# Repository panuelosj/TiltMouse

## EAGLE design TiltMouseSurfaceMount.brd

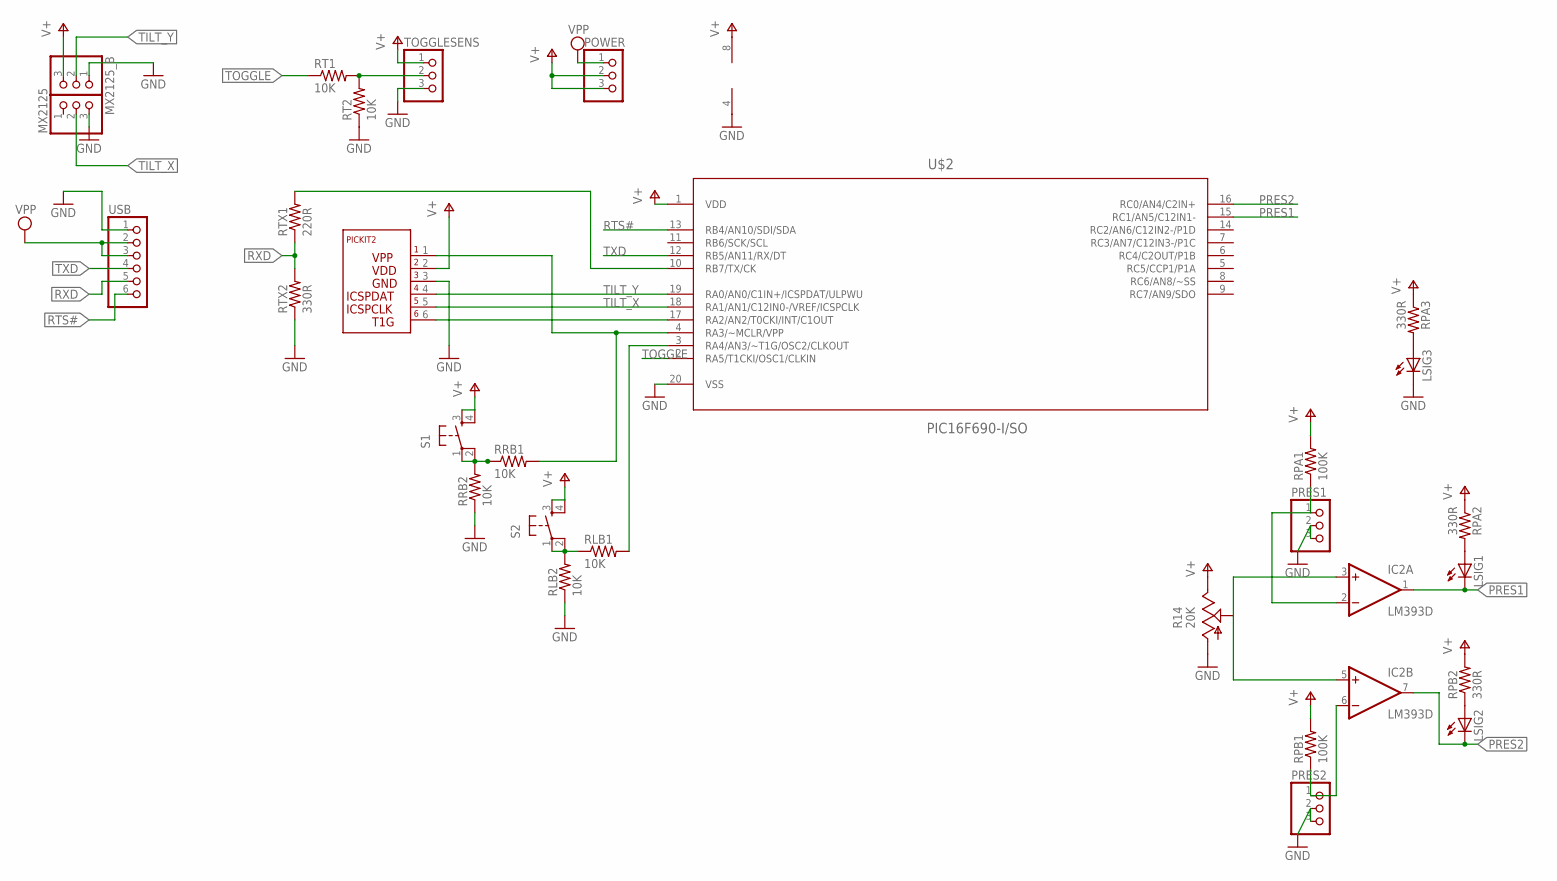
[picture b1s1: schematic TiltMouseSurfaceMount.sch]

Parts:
IC2: LM393D; SO08
LSIG1, LSIG2, LSIG3: LEDSMT1206; 1206
MX2125, MX2125_B: PINHD-1X3; 1X03
POWER: PINHD-1X3; 1X03
PRES1, PRES2: PINHD-1X3/90; 1X03/90
R14: 20K; SM-42/43A
RLB1, RLB2: 10K; R0805
RPA1: 100K; R0805
RPA2, RPA3: 330R; R0805
RPB1: 100K; R0805
RPB2: 330R; R0805
RRB1, RRB2: 10K; R0805
RT1, RT2: 10K; R0805
RTX1: 220R; R0805
RTX2: 330R; R0805
S1, S2: TAC_SWITCHSMD; TACTILE_SWITCH_SMD
TOGGLESENS: PINHD-1X3; 1X03
U$2: PIC16F690-I/SO; SOIC127P1030X265-20N
U$3: PICKIT-ICSP; PICKITJUMPER
USB: PINHD-1X6/90; 1X06/90

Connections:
GND: IC2.4 (V-), LSIG3.C, MX2125.3, MX2125_B.1, PRES1.2, PRES1.3, PRES2.2, PRES2.3, R14.1 (A), RLB2.1, RRB2.1, RT2.1, RTX2.1, TOGGLESENS.3, U$2.20 (VSS), U$3.3, USB.1
unnamed: RT1.2, RT2.2, TOGGLESENS.2
unnamed: IC2.2 (-IN), PRES1.1, RPA1.1
unnamed: RTX1.2, U$2.10 (RB7/TX/CK)
unnamed: RRB1.1, RRB2.2, S1.1, S1.2
unnamed: RLB1.1, RLB2.2, S2.1, S2.2
unnamed: RLB1.2, U$2.3 (RA4/AN3/~T1G/OSC2/CLKOUT)
unnamed: IC2.6 (-IN), PRES2.1, RPB1.1
unnamed: IC2.3 (+IN), IC2.5 (+IN), R14.2 (S)
unnamed: LSIG2.A, RPB2.1
unnamed: LSIG1.A, RPA2.2
unnamed: LSIG3.A, RPA3.2
unnamed: RRB1.2, U$2.4 (RA3/~MCLR/VPP), U$3.1
unnamed: U$2.17 (RA2/AN2/T0CKI/INT/C1OUT), U$3.6
PRES1: IC2.1 (OUT), LSIG1.C, U$2.15 (RC1/AN5/C12IN1-)
PRES2: IC2.7 (OUT), LSIG2.C, U$2.16 (RC0/AN4/C2IN+)
RTS#: U$2.13 (RB4/AN10/SDI/SDA), USB.6
RXD: RTX1.1, RTX2.2, USB.5
TILT_X: MX2125.2, U$2.18 (RA1/AN1/C12IN0-/VREF/ICSPCLK), U$3.5
TILT_Y: MX2125_B.2, U$2.19 (RA0/AN0/C1IN+/ICSPDAT/ULPWU), U$3.4
TOGGLE: RT1.1, U$2.2 (RA5/T1CKI/OSC1/CLKIN)
TXD: U$2.12 (RB5/AN11/RX/DT), USB.4
V+: IC2.8 (V+), MX2125_B.3, POWER.2, POWER.3, R14.3 (E), RPA1.2, RPA2.1, RPA3.1, RPB1.2, RPB2.2, S1.3, S1.4, S2.3, S2.4, TOGGLESENS.1, U$2.1 (VDD), U$3.2
VPP: POWER.1, USB.2, USB.3

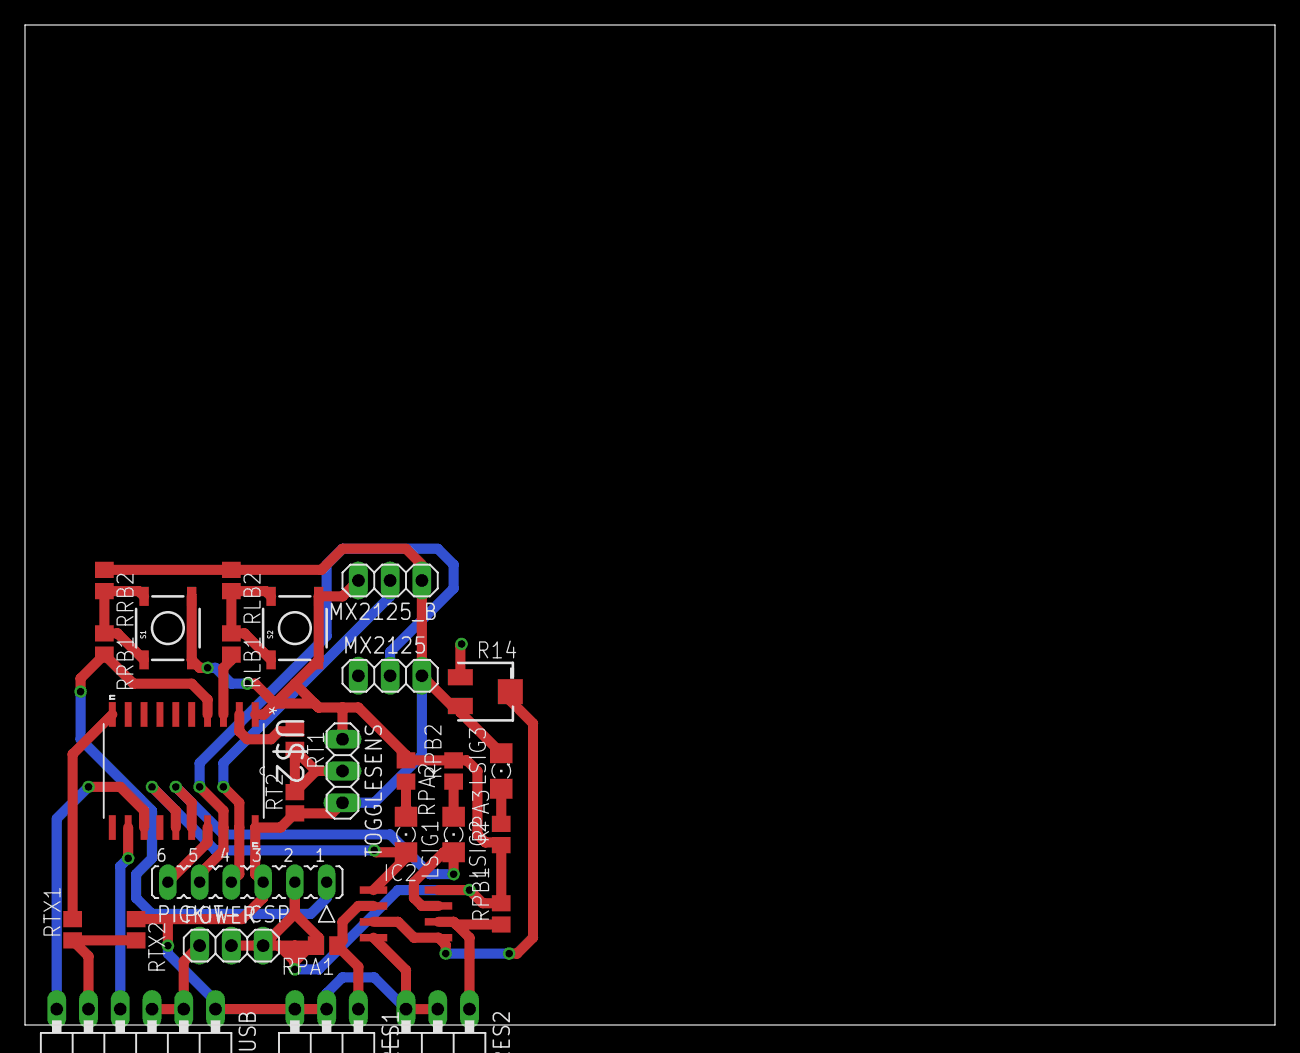
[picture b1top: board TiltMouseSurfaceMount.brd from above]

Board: 2 copper layers, 100.0 x 80.0 mm, 29 parts (0 on the bottom side), 24 nets.

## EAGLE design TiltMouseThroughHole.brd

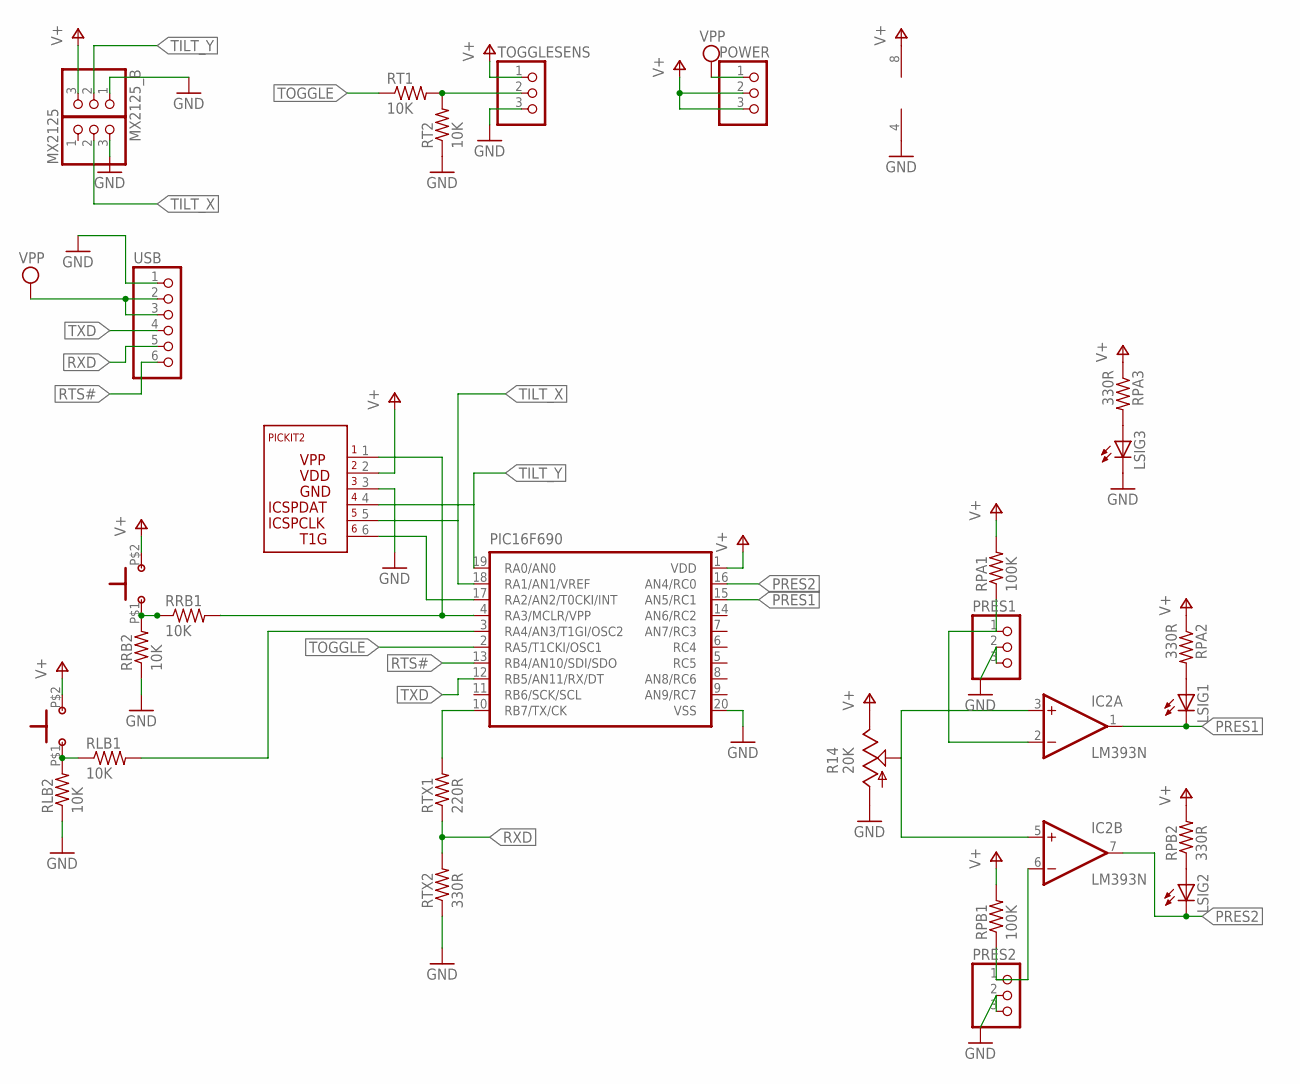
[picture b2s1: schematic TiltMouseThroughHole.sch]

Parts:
IC2: LM393N; DIL08
LB: PUSHBUTTON
LSIG1, LSIG2, LSIG3: LED5MM
MX2125, MX2125_B: PINHD-1X3; 1X03
PIC16F690: PIC16F6XX; DIL20
POWER: PINHD-1X3; 1X03
PRES1, PRES2: PINHD-1X3/90; 1X03/90
R14: 20K; B25P
RB: PUSHBUTTON
RLB1, RLB2: 10K; 0207/12
RPA1: 100K; 0207/10
RPA2: 330R; 0207/15
RPA3: 330R; 0207/10
RPB1: 100K; 0207/10
RPB2: 330R; 0207/15
RRB1, RRB2: 10K; 0207/12
RT1, RT2: 10K; 0207/10
RTX1: 220R; 0207/15
RTX2: 330R; 0207/15
TOGGLESENS: PINHD-1X3; 1X03
U$1: PICKIT-ICSP; PICKITJUMPER
USB: PINHD-1X6/90; 1X06/90

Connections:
GND: IC2.4 (V-), LSIG3.K (C), MX2125.3, MX2125_B.1, PIC16F690.20 (VSS), PRES1.2, PRES1.3, PRES2.2, PRES2.3, R14.A, RLB2.1, RRB2.1, RT2.1, RTX2.1, TOGGLESENS.3, U$1.3, USB.1
unnamed: PIC16F690.4 (RA3/MCLR/VPP), RRB1.2, U$1.1
unnamed: RT1.2, RT2.2, TOGGLESENS.2
unnamed: IC2.2 (-IN), PRES1.1, RPA1.1
unnamed: PIC16F690.17 (RA2/AN2/T0CKI/INT), U$1.6
unnamed: PIC16F690.10 (RB7/TX/CK), RTX1.2
unnamed: RB.P$1 (1), RRB1.1, RRB2.2
unnamed: LB.P$1 (1), RLB1.1, RLB2.2
unnamed: PIC16F690.3 (RA4/AN3/T1GI/OSC2), RLB1.2
unnamed: IC2.6 (-IN), PRES2.1, RPB1.1
unnamed: IC2.3 (+IN), IC2.5 (+IN), R14.S
unnamed: LSIG2.A, RPB2.1
unnamed: LSIG1.A, RPA2.2
unnamed: LSIG3.A, RPA3.2
PRES1: IC2.1 (OUT), LSIG1.K (C), PIC16F690.15 (AN5/RC1)
PRES2: IC2.7 (OUT), LSIG2.K (C), PIC16F690.16 (AN4/RC0)
RTS#: PIC16F690.13 (RB4/AN10/SDI/SDO), USB.6
RXD: RTX1.1, RTX2.2, USB.5
TILT_X: MX2125.2, PIC16F690.18 (RA1/AN1/VREF), U$1.5
TILT_Y: MX2125_B.2, PIC16F690.19 (RA0/AN0), U$1.4
TOGGLE: PIC16F690.2 (RA5/T1CKI/OSC1), RT1.1
TXD: PIC16F690.12 (RB5/AN11/RX/DT), USB.4
V+: IC2.8 (V+), LB.P$2 (2), MX2125_B.3, PIC16F690.1 (VDD), POWER.2, POWER.3, R14.E, RB.P$2 (2), RPA1.2, RPA2.1, RPA3.1, RPB1.2, RPB2.2, TOGGLESENS.1, U$1.2
VPP: POWER.1, USB.2, USB.3

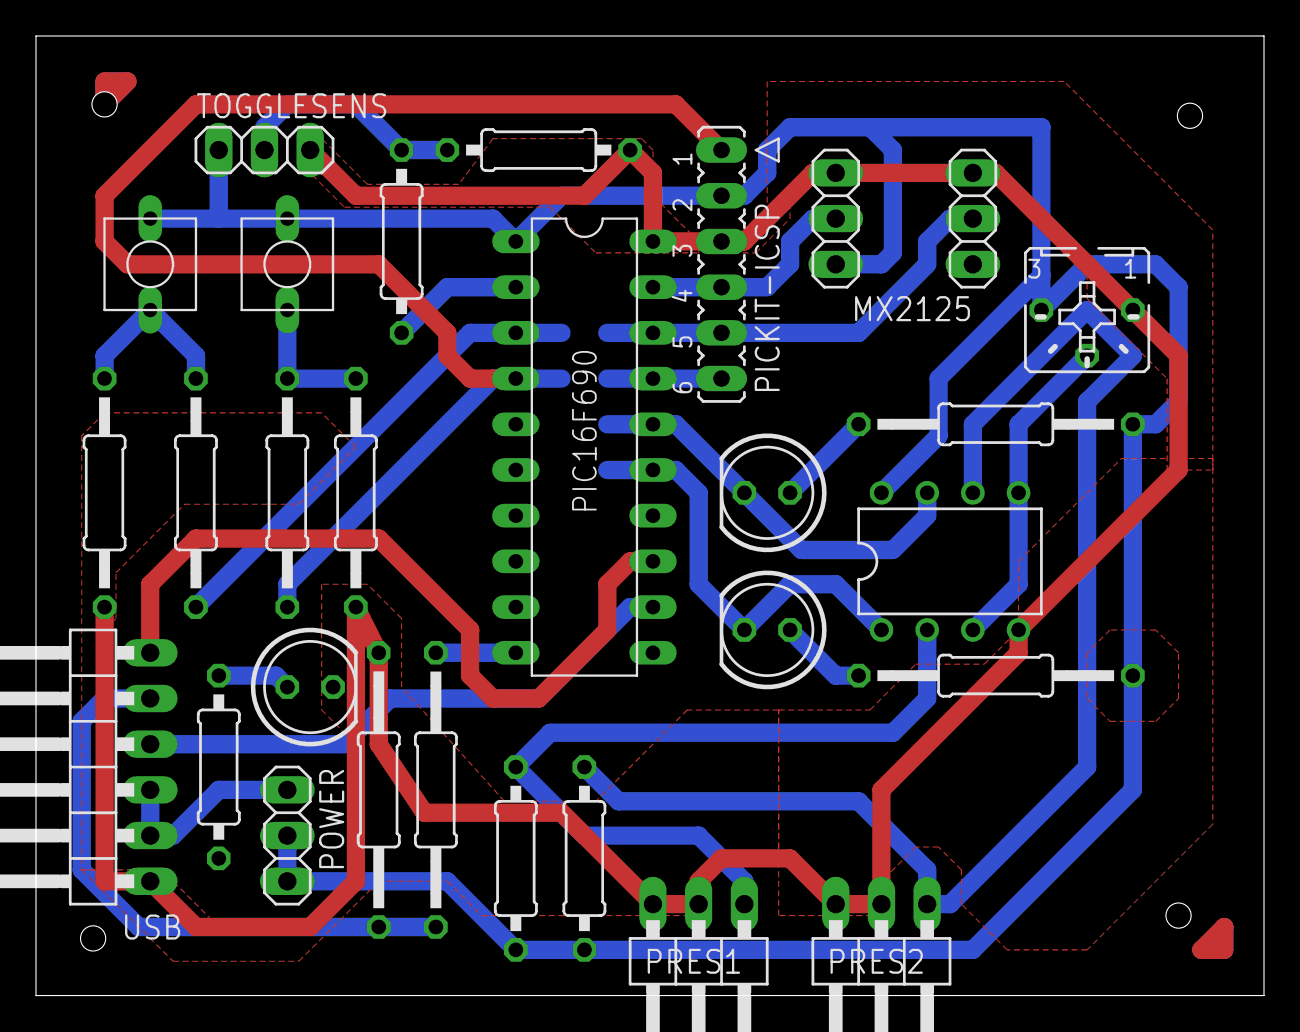
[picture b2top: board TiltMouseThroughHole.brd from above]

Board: 2 copper layers, 68.2 x 53.3 mm, 29 parts (0 on the bottom side), 24 nets.

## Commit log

2017-02-10 finished project from high school
